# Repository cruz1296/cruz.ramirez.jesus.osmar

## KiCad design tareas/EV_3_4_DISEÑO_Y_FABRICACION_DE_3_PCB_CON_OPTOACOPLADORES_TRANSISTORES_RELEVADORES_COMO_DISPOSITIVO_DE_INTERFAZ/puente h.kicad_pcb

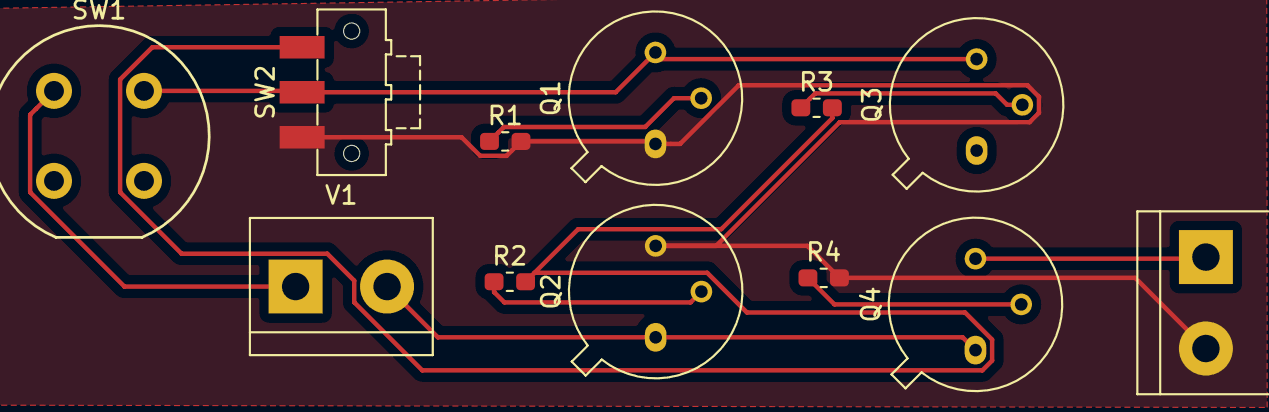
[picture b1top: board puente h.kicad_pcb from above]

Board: 2 copper layers, 12 parts (0 on the bottom side), 10 nets.

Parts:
M1: Motor_DC; TerminalBlock_bornier-2_P5.08mm
Q1, Q2, Q3, Q4: 2N2219; TO-39-3
R1, R2, R3, R4: R; R_0603_1608Metric_Pad1.05x0.95mm_HandSolder
SW1: SW_SPST; Push_E-Switch_KS01Q01
SW2: SW_SPDT; SW_SPDT_CK-JS102011SAQN
V1: VSOURCE; TerminalBlock_bornier-2_P5.08mm

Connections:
unnamed: M1.1, Q4.3
unnamed: M1.2, Q1.1, Q2.3, R1.2, R4.2, SW2.1
unnamed: Q1.2, R1.1
unnamed: Q1.3, Q3.3, SW1.2, SW2.2
unnamed: Q2.1, Q4.1, V1.2
unnamed: Q2.2, R2.1
unnamed: Q3.2, R3.1
unnamed: Q4.2, R4.1
unnamed: R2.2, R3.2, SW2.3
unnamed: SW1.1, V1.1

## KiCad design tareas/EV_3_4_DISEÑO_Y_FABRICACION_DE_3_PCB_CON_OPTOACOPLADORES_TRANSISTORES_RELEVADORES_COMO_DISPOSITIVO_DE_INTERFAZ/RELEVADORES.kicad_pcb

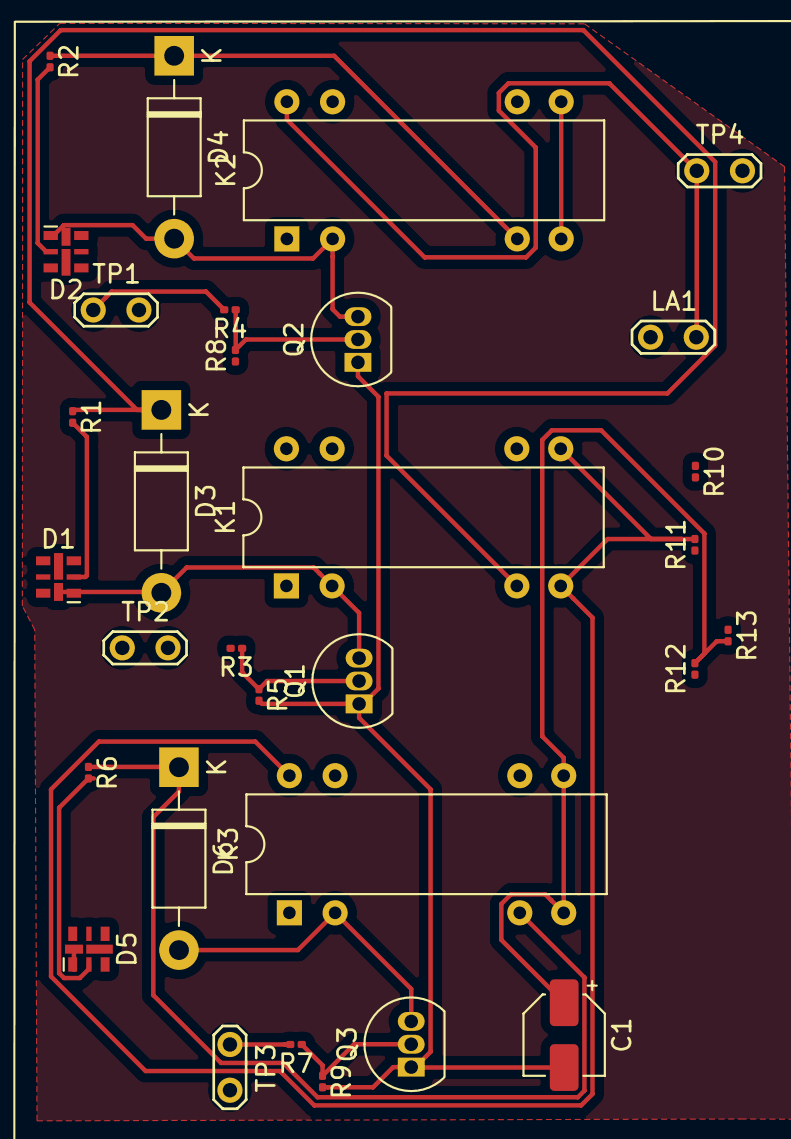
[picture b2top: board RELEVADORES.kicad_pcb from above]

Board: 2 copper layers, 31 parts (0 on the bottom side), 20 nets.

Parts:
C1: C; CP_Elec_4x4.5
D1, D2, D5: LED; LED-APA102-2020
D3, D4, D6: 1N4001; D_DO-41_SOD81_P10.16mm_Horizontal
K1, K2, K3: DIPxx-1Cxx-51x; Relay_StandexMeder_DIP_LowProfile
LA1: Lamp; TestPoint_2Pads_Pitch2.54mm_Drill0.8mm
Q1, Q2, Q3: 2N3904; TO-92_Inline
R1, R2, R3, R4, R5, R6, R7, R8, R9, R10, R11, R12, R13: R; R_0201_0603Metric
TP1, TP2, TP3, TP4: TestPoint; TestPoint_2Pads_Pitch2.54mm_Drill0.8mm

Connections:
GND: C1.2, Q1.1, Q2.1, Q3.1, R5.2, R8.1, R9.2
unnamed: C1.1, K3.7, K3.8, R12.2, R13.2
unnamed: D1.1, D3.2, K1.2, Q1.3
unnamed: D1.2, R1.2
unnamed: D2.1, D4.2, K2.2, Q2.3
unnamed: D2.2, R2.2
unnamed: D3.1, K1.6, R1.1
unnamed: D4.1, K2.6, R2.1
unnamed: D5.1, D6.2, K3.2, Q3.3
unnamed: D5.2, R6.2
unnamed: D6.1, K3.6, R6.1
unnamed: K1.7, K1.8, K3.14, R11.2, R12.1
unnamed: K1.14, K2.7, K2.8, R10.2, R11.1
unnamed: K2.14, LA1.2, R10.1, TP4.1
unnamed: Q1.2, R3.1, R5.1
unnamed: Q2.2, R4.1, R8.2
unnamed: Q3.2, R7.1, R9.1
unnamed: R3.2, TP2.1
unnamed: R4.2, TP1.1
unnamed: R7.2, TP3.1

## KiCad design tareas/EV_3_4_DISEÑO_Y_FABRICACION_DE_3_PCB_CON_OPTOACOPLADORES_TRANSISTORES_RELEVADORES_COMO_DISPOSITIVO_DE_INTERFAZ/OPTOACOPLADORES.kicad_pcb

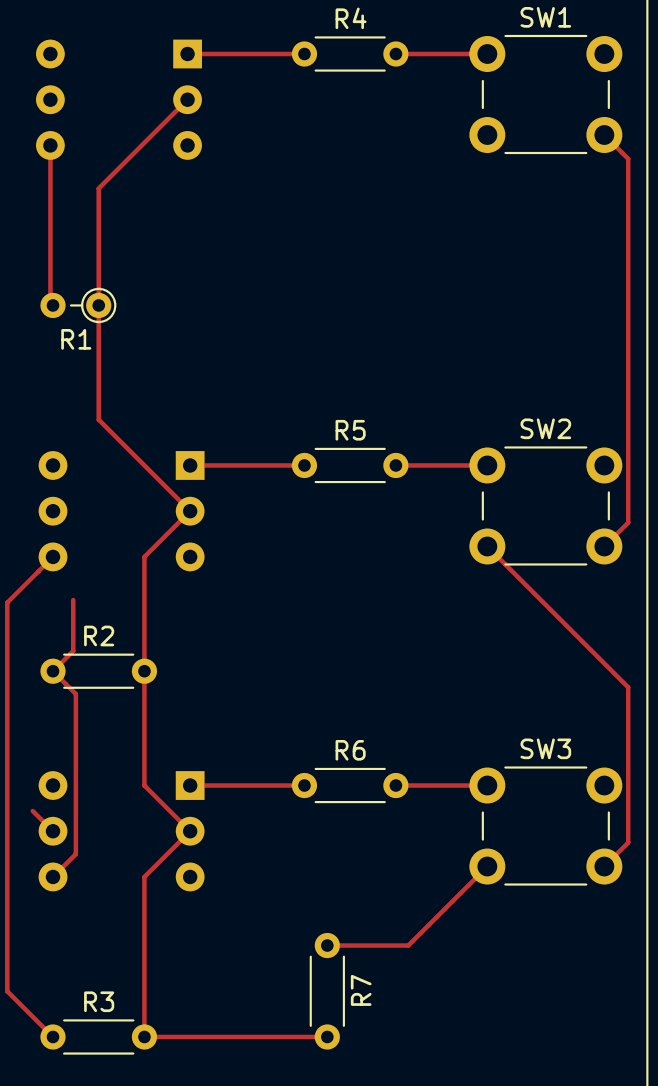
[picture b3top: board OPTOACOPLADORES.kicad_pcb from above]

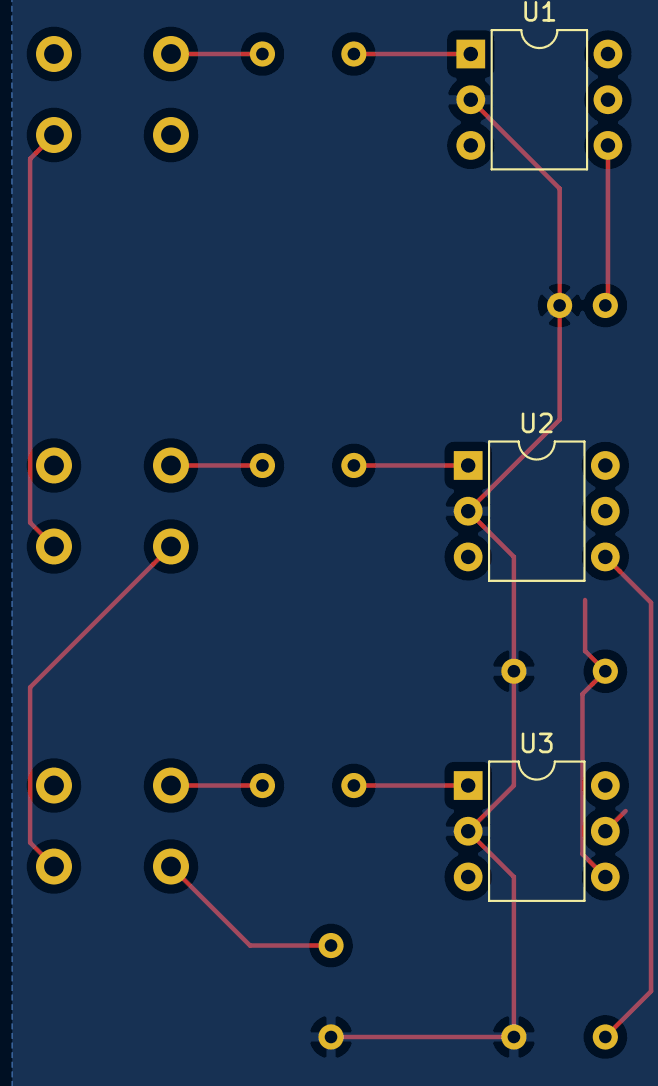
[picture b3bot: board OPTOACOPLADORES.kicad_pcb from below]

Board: 2 copper layers, 13 parts (3 on the bottom side), 11 nets.

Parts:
R1: R; R_Axial_DIN0204_L3.6mm_D1.6mm_P2.54mm_Vertical
R2, R3, R4, R5, R6, R7: R; R_Axial_DIN0204_L3.6mm_D1.6mm_P5.08mm_Horizontal
SW1, SW2, SW3: SW_Push; SW_PUSH_6mm
U1, U2, U3: 4N25; DIP-6_W7.62mm

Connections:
GND: R1.1, R2.2, R3.2, R7.2, U1.2, U2.2, U3.2
unnamed: R1.2, U1.4
unnamed: R2.1, U3.4
unnamed: R3.1, U2.4
unnamed: R4.1, U1.1
unnamed: R4.2, SW1.1
unnamed: R5.1, U2.1
unnamed: R5.2, SW2.1
unnamed: R6.1, U3.1
unnamed: R6.2, SW3.1
VCC: R7.1, SW1.2, SW2.2, SW3.2
